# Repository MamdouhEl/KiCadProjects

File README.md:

# KiCadProjects
This repo has pcb design projects

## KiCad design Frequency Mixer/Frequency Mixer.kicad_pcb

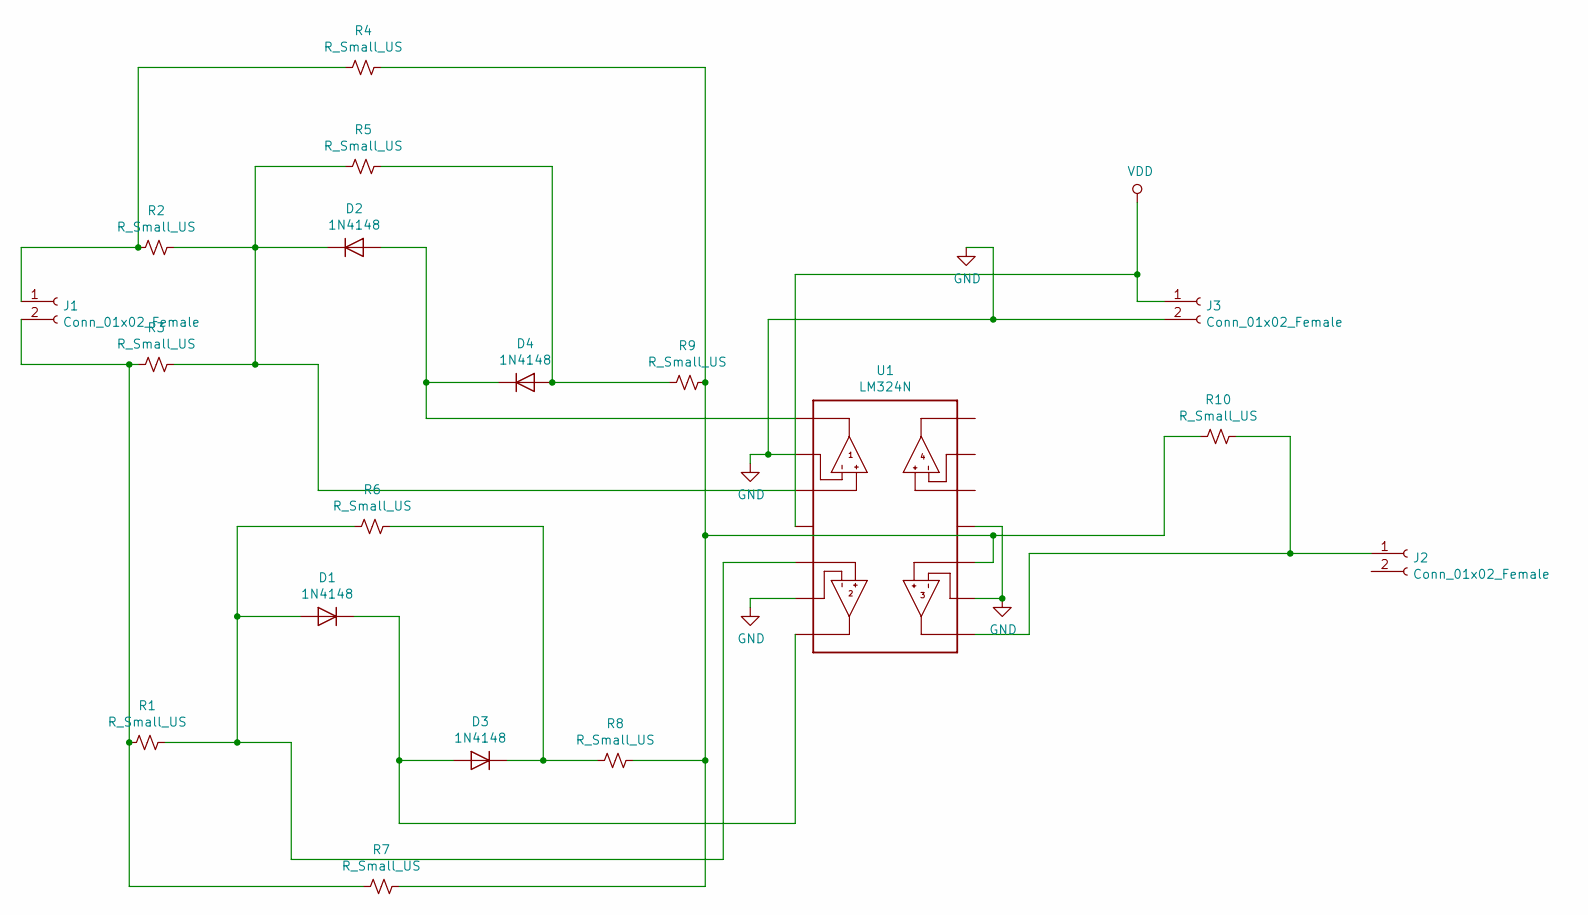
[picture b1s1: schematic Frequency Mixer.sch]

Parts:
D1, D2, D3, D4: 1N4148; D_DO-35_SOD27_P7.62mm_Horizontal
J1, J2, J3: Conn_01x02_Female; TerminalBlock_bornier-2_P5.08mm
R1, R2, R3, R4, R5, R6, R7, R8, R9, R10: R_Small_US; R_Axial_DIN0204_L3.6mm_D1.6mm_P5.08mm_Horizontal
U1: LM324N; DIP762W45P254L1969H508Q14

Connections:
GND: J3.2, U1.2 (1IN-), U1.6 (2IN-), U1.9 (3IN-), U1.11 (GND)
unnamed: D1.1 (K), D3.2 (A), U1.7 (2OUT)
unnamed: D1.2 (A), R1.1, R6.2, U1.5 (2IN+)
unnamed: D2.1 (K), R2.1, R3.1, R5.2, U1.3 (1IN+)
unnamed: D2.2 (A), D4.1 (K), U1.1 (1OUT)
unnamed: D3.1 (K), R6.1, R8.2
unnamed: D4.2 (A), R5.1, R9.2
unnamed: J1.1, R2.2, R4.2
unnamed: J1.2, R1.2, R3.2, R7.2
unnamed: J2.1, R10.1, U1.8 (3OUT)
unnamed: R4.1, R7.1, R8.1, R9.1, R10.2, U1.10 (3IN+)
VDD: J3.1, U1.4 (VCC)

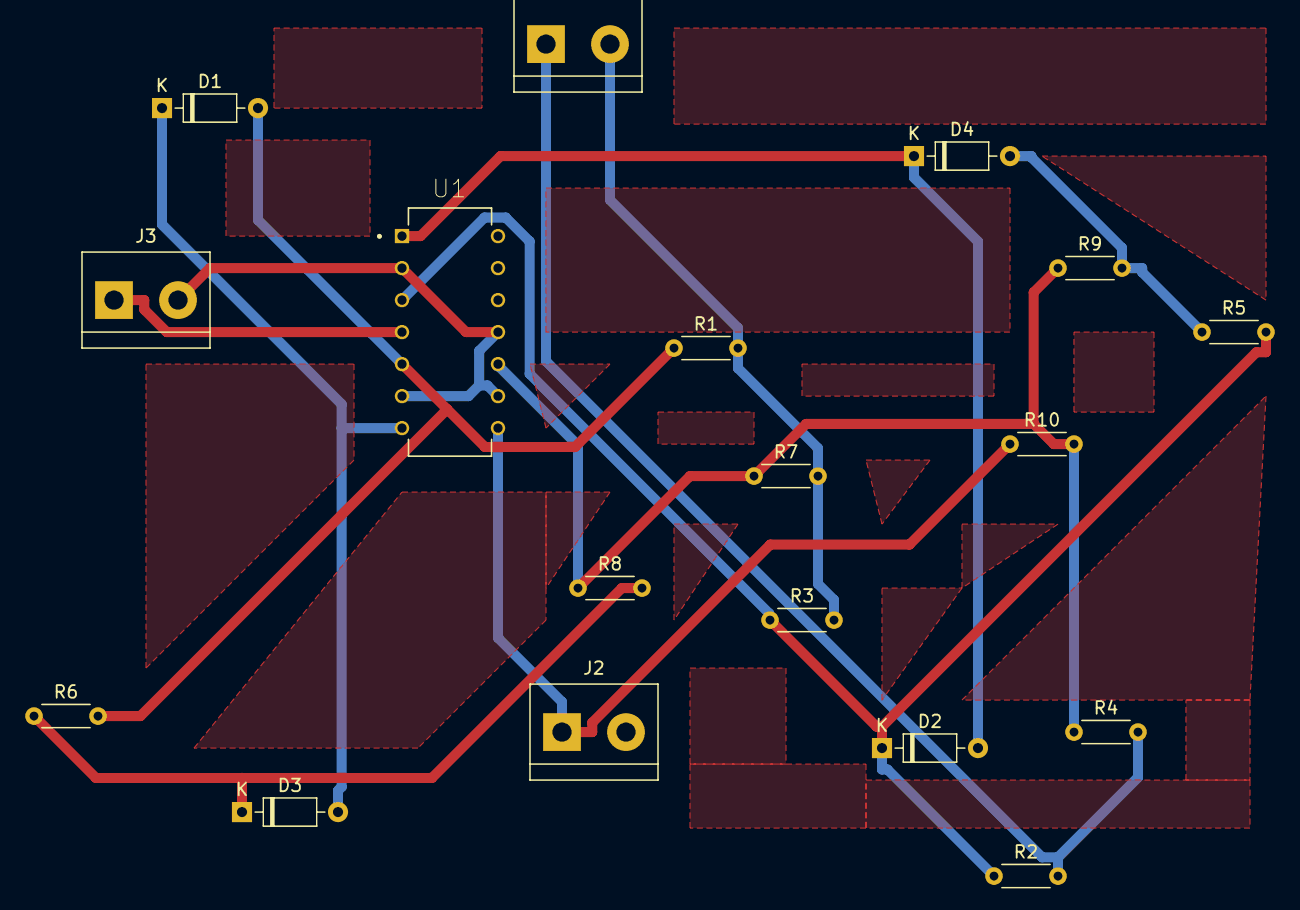
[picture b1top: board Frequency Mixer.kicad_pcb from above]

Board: 2 copper layers, 18 parts (0 on the bottom side), 12 nets.

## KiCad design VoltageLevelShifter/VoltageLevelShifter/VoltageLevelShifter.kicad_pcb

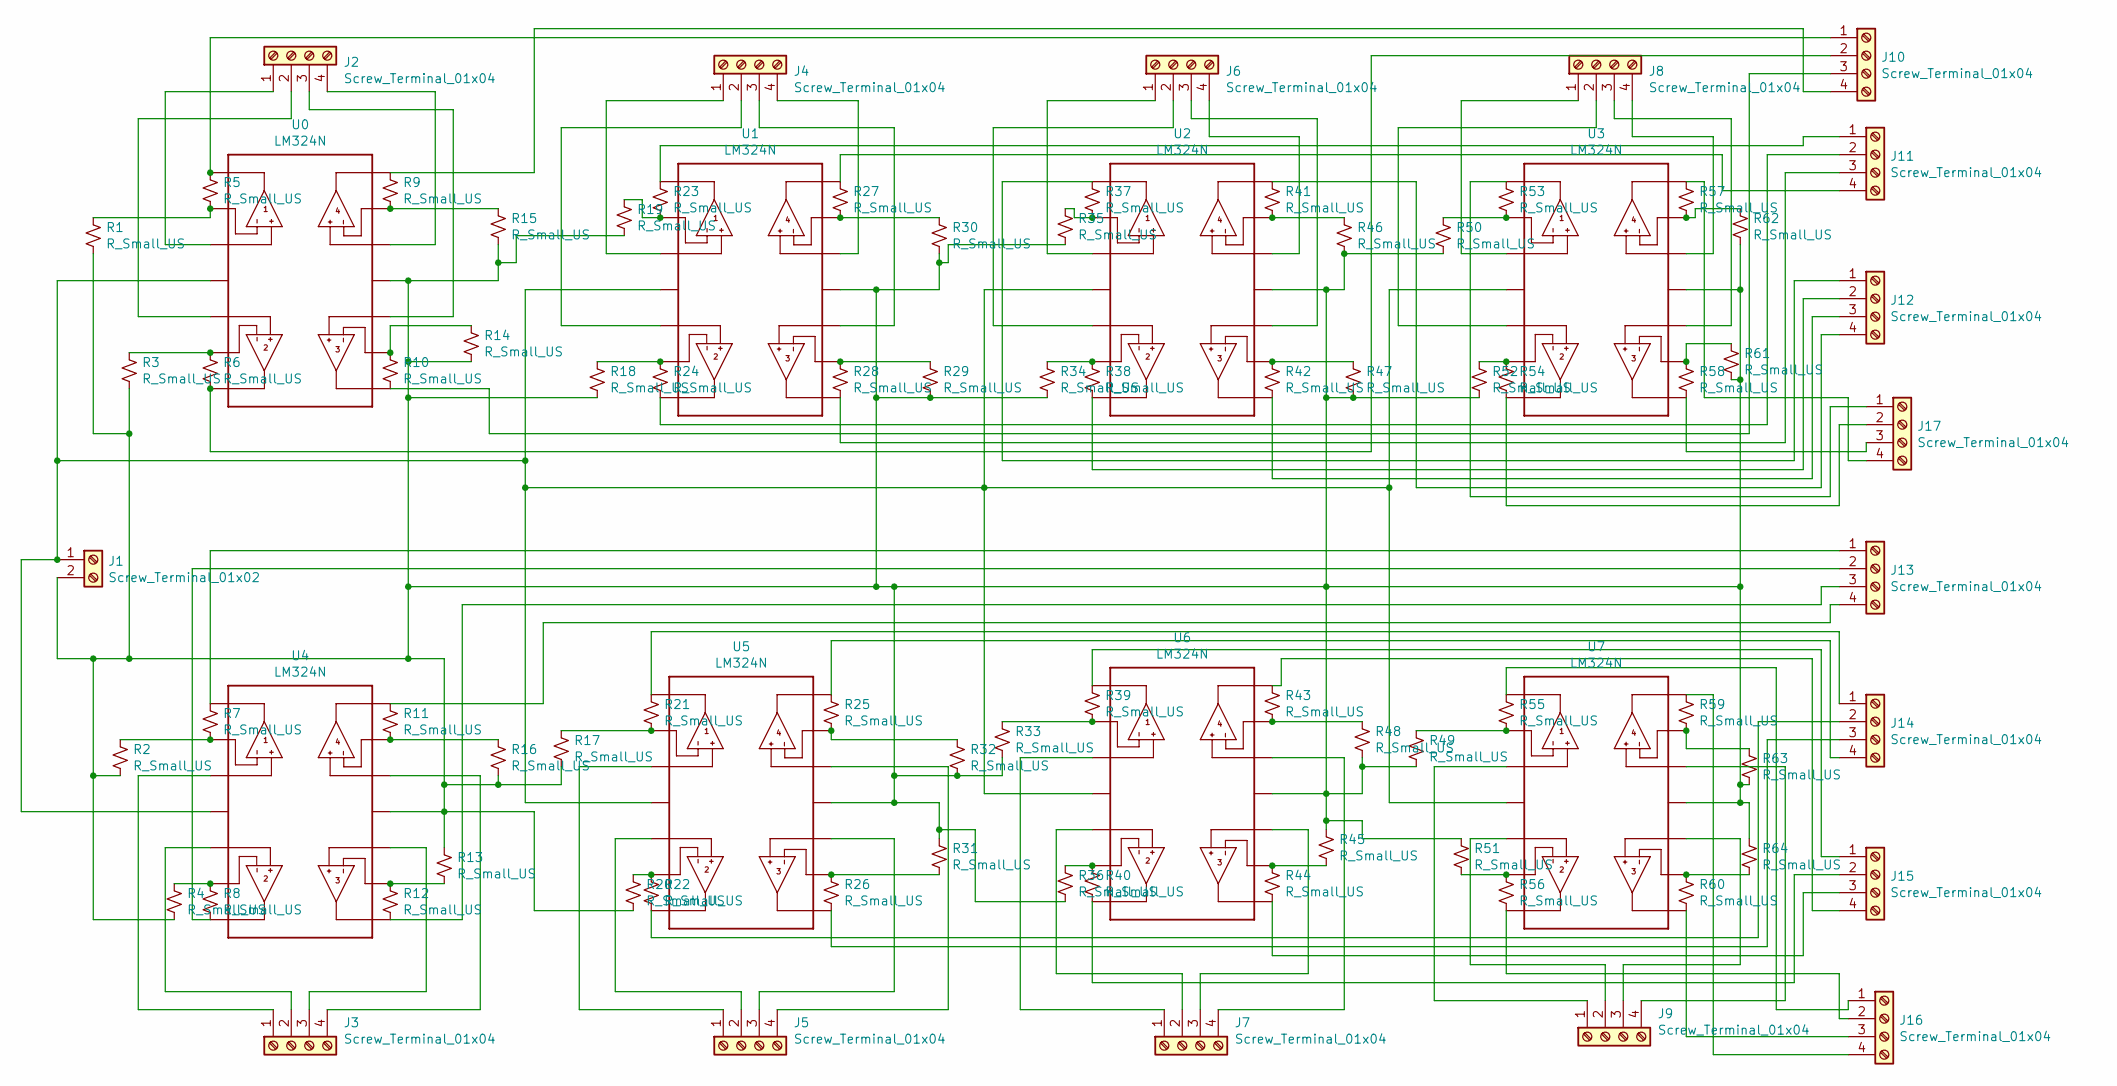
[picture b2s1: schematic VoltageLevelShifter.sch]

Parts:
J1: Screw_Terminal_01x02; TerminalBlock_WAGO_236-102_1x02_P5.00mm_45Degree
J2, J3, J4, J5, J6, J7, J8, J9, J10, J11, J12, J13, J14, J15, J16, J17: Screw_Terminal_01x04; TerminalBlock_WAGO_236-104_1x04_P5.00mm_45Degree
R1, R2, R3, R4, R5, R6, R7, R8, R9, R10, R11, R12, R13, R14, R15, R16, R17, R18, R19, R20, R21, R22, R23, R24, R25, R26, R27, R28, R29, R30, R31, R32, R33, R34, R35, R36, R37, R38, R39, R40, R41, R42, R43, R44, R45, R46, R47, R48, R49, R50, R51, R52, R53, R54, R55, R56, R57, R58, R59, R60, R61, R62, R63, R64: R_Small_US; RESAD640W45L370D200
U0, U1, U2, U3, U4, U5, U6, U7: LM324N; DIP762W45P254L1969H508Q14

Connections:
unnamed: J1.1, U0.4 (VCC), U1.4 (VCC), U2.4 (VCC), U3.4 (VCC), U4.4 (VCC), U5.4 (VCC), U6.4 (VCC), U7.4 (VCC)
unnamed: J1.2, R1.2, R2.2, R3.2, R4.2, R13.1, R14.2, R15.2, R16.2, R17.2, R18.2, R19.2, R20.2, R29.2, R30.2, R31.1, R32.2, R33.2, R34.2, R35.2, R36.2, R45.1, R46.2, R47.2, R48.2, R49.2, R50.2, R51.1, R52.2, R61.2, R62.2, R63.2, R64.1, U0.11 (GND), U1.11 (GND), U2.11 (GND), U3.11 (GND), U4.11 (GND), U5.11 (GND), U6.11 (GND), U7.11 (GND)
unnamed: J2.1, U0.3 (1IN+)
unnamed: J2.2, U0.5 (2IN+)
unnamed: J2.3, U0.10 (3IN+)
unnamed: J2.4, U0.12 (4IN+)
unnamed: J3.1, U4.3 (1IN+)
unnamed: J3.2, U4.5 (2IN+)
unnamed: J3.3, U4.10 (3IN+)
unnamed: J3.4, U4.12 (4IN+)
unnamed: J4.1, U1.3 (1IN+)
unnamed: J4.2, U1.5 (2IN+)
unnamed: J4.3, U1.10 (3IN+)
unnamed: J4.4, U1.12 (4IN+)
unnamed: J5.1, U5.3 (1IN+)
unnamed: J5.2, U5.5 (2IN+)
unnamed: J5.3, U5.10 (3IN+)
unnamed: J5.4, U5.12 (4IN+)
unnamed: J6.1, U2.3 (1IN+)
unnamed: J6.2, U2.5 (2IN+)
unnamed: J6.3, U2.10 (3IN+)
unnamed: J6.4, U2.12 (4IN+)
unnamed: J7.1, U6.3 (1IN+)
unnamed: J7.2, U6.5 (2IN+)
unnamed: J7.3, U6.10 (3IN+)
unnamed: J7.4, U6.12 (4IN+)
unnamed: J8.1, U3.3 (1IN+)
unnamed: J8.2, U3.5 (2IN+)
unnamed: J8.3, U3.10 (3IN+)
unnamed: J8.4, U3.12 (4IN+)
unnamed: J9.1, U7.3 (1IN+)
unnamed: J9.2, U7.5 (2IN+)
unnamed: J9.3, U7.10 (3IN+)
unnamed: J9.4, U7.12 (4IN+)
unnamed: J10.1, R5.1, U0.1 (1OUT)
unnamed: J10.2, R6.2, U0.7 (2OUT)
unnamed: J10.3, R10.2, U0.8 (3OUT)
unnamed: J10.4, R9.1, U0.14 (4OUT)
unnamed: J11.1, R23.1, U1.1 (1OUT)
unnamed: J11.2, R24.2, U1.7 (2OUT)
unnamed: J11.3, R28.2, U1.8 (3OUT)
unnamed: J11.4, R27.1, U1.14 (4OUT)
unnamed: J12.1, R37.1, U2.1 (1OUT)
unnamed: J12.2, R38.2, U2.7 (2OUT)
unnamed: J12.3, R42.2, U2.8 (3OUT)
unnamed: J12.4, R41.1, U2.14 (4OUT)
unnamed: J13.1, R7.1, U4.1 (1OUT)
unnamed: J13.2, R8.2, U4.7 (2OUT)
unnamed: J13.3, R12.2, U4.8 (3OUT)
unnamed: J13.4, R11.1, U4.14 (4OUT)
unnamed: J14.1, R21.1, U5.1 (1OUT)
unnamed: J14.2, R22.2, U5.7 (2OUT)
unnamed: J14.3, R26.2, U5.8 (3OUT)
unnamed: J14.4, R25.1, U5.14 (4OUT)
unnamed: J15.1, R39.1, U6.1 (1OUT)
unnamed: J15.2, R40.2, U6.7 (2OUT)
unnamed: J15.3, R44.2, U6.8 (3OUT)
unnamed: J15.4, R43.1, U6.14 (4OUT)
unnamed: J16.1, R55.1, U7.1 (1OUT)
unnamed: J16.2, R56.2, U7.7 (2OUT)
unnamed: J16.3, R60.2, U7.8 (3OUT)
unnamed: J16.4, R59.1, U7.14 (4OUT)
unnamed: J17.1, R53.1, U3.1 (1OUT)
unnamed: J17.2, R54.2, U3.7 (2OUT)
unnamed: J17.3, R58.2, U3.8 (3OUT)
unnamed: J17.4, R57.1, U3.14 (4OUT)
unnamed: R1.1, R5.2, U0.2 (1IN-)
unnamed: R2.1, R7.2, U4.2 (1IN-)
unnamed: R3.1, R6.1, U0.6 (2IN-)
unnamed: R4.1, R8.1, U4.6 (2IN-)
unnamed: R10.1, R14.1, U0.9 (3IN-)
unnamed: R11.2, R16.1, U4.13 (4IN-)
unnamed: R12.1, R13.2, U4.9 (3IN-)
unnamed: R9.2, R15.1, U0.13 (4IN-)
unnamed: R17.1, R21.2, U5.2 (1IN-)
unnamed: R18.1, R24.1, U1.6 (2IN-)
unnamed: R19.1, R23.2, U1.2 (1IN-)
unnamed: R20.1, R22.1, U5.6 (2IN-)
unnamed: R25.2, R32.1, U5.13 (4IN-)
unnamed: R26.1, R31.2, U5.9 (3IN-)
unnamed: R27.2, R30.1, U1.13 (4IN-)
unnamed: R28.1, R29.1, U1.9 (3IN-)
unnamed: R33.1, R39.2, U6.2 (1IN-)
unnamed: R34.1, R38.1, U2.6 (2IN-)
unnamed: R35.1, R37.2, U2.2 (1IN-)
unnamed: R36.1, R40.1, U6.6 (2IN-)
unnamed: R41.2, R46.1, U2.13 (4IN-)
unnamed: R42.1, R47.1, U2.9 (3IN-)
unnamed: R43.2, R48.1, U6.13 (4IN-)
unnamed: R44.1, R45.2, U6.9 (3IN-)
unnamed: R49.1, R55.2, U7.2 (1IN-)
unnamed: R50.1, R53.2, U3.2 (1IN-)
unnamed: R51.2, R56.1, U7.6 (2IN-)
unnamed: R52.1, R54.1, U3.6 (2IN-)
unnamed: R57.2, R62.1, U3.13 (4IN-)
unnamed: R58.1, R61.1, U3.9 (3IN-)
unnamed: R59.2, R63.1, U7.13 (4IN-)
unnamed: R60.1, R64.2, U7.9 (3IN-)

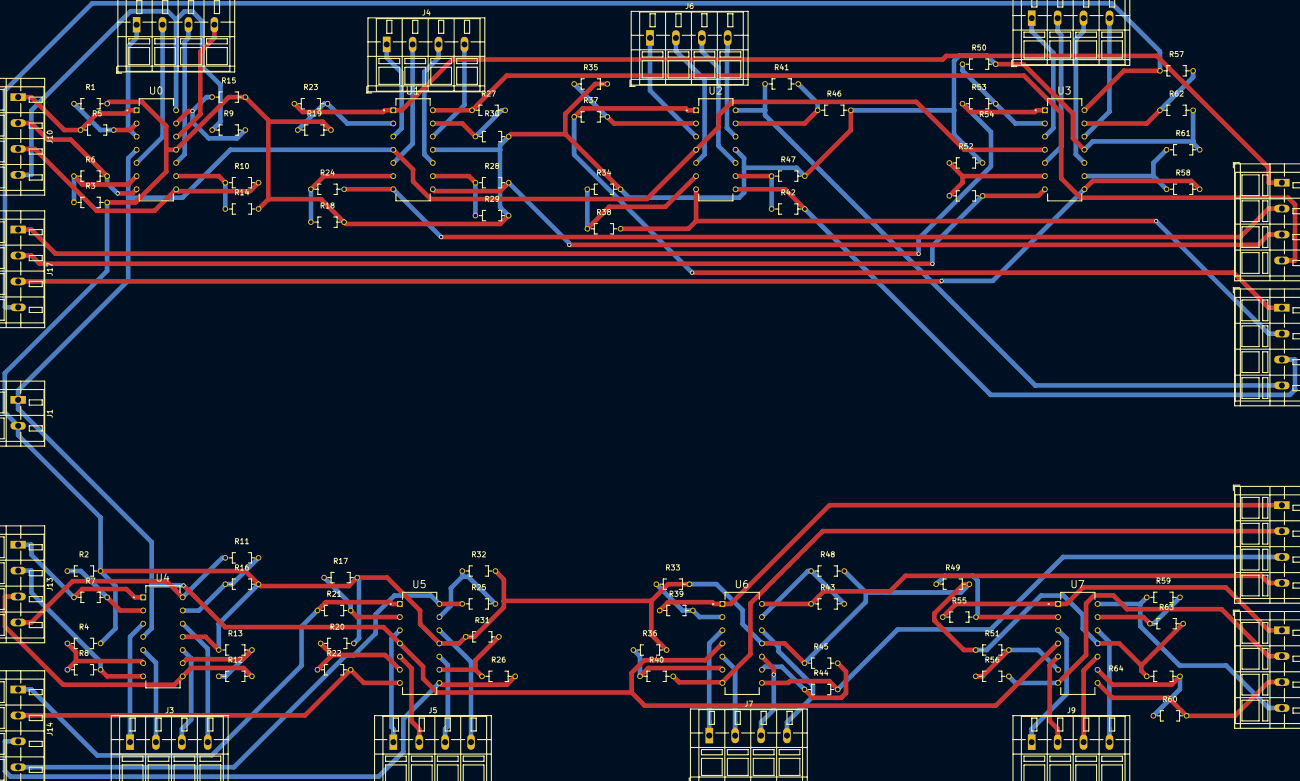
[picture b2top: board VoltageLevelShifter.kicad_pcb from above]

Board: 2 copper layers, 89 parts (0 on the bottom side), 98 nets.
